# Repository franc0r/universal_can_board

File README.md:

# universal_can_board
Contains schematic, pcb layout and software of the francor's universal can board.

# Description
The universal board is used to control and monitor several components of a mobile robot like the motor controllers, co2 sensors, pan tilt unit, etc...

The board communicates via CAN interface. The used µC is a AVR from the Arduino Nano v2. Future more this board is based on an Arduino, so the Arduino IDE can be used to programm the board.

# Requirements
## Motor Controller
The BLD300B motor controller is used to drive the Robot Morty. This controller must be controlled and monitored by the board. For this following inputs and outputs are required.

* Input
  * An analog to measure current voltage of the motor controller.
  * An analog to measure current current of the motor controller.
  * Three digital to get the hall sensors of the hub motor wheels.
  * An digital to get the speed ticks from the motor controller.
* Output
  * An PWM to set the motor power.
  * An digital to set the rotation direction.
  * An digital to enable/disable the break.
  * An digital to enable/disable the motor controller.
  
## CO2 Sensor
The universal board should be able to measure the CO2 sensor and publish the values via CAN.

* Input
  * An analog to measure the current CO2 concentration.
  
* Output
  * An digital to indicate a high CO2 concentration. (drive a LED).

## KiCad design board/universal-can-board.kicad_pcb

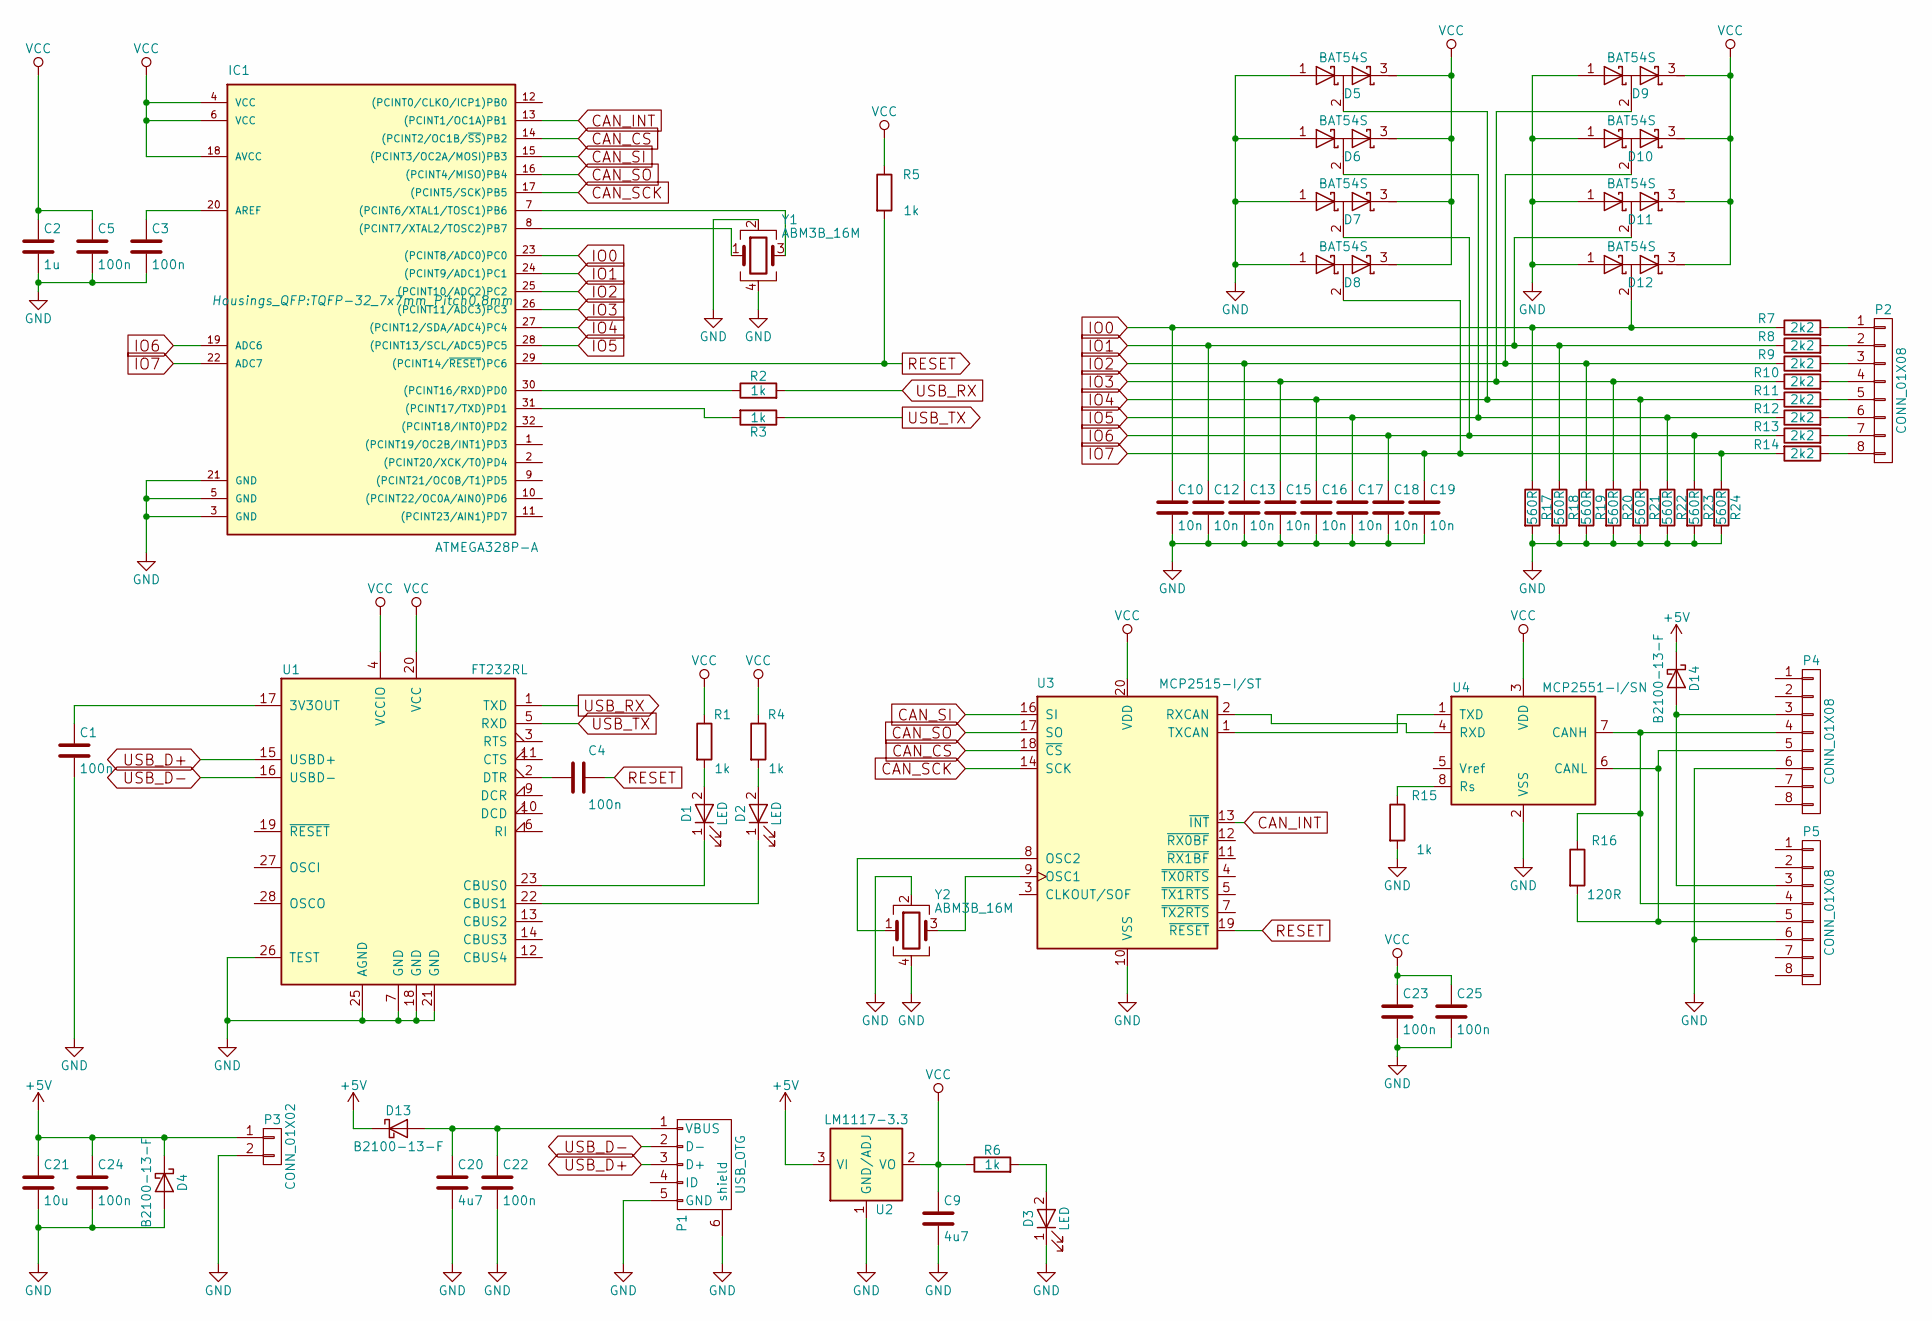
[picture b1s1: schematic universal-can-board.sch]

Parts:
C1, C3, C4, C5, C22, C23, C24, C25: 100n; C_0805
C2: 1u; C_0805
C9, C20: 4u7; C_1210
C10, C12, C13, C15, C16, C17, C18, C19: 10n; C_0805
C21: 10u; C_1210
D1, D2, D3: LED; LED_0805
D4, D13, D14: B2100-13-F; SMB_Standard
D5, D6, D7, D8, D9, D10, D11, D12: BAT54S; SOT-23
IC1: ATMEGA328P-A; TQFP-32_7x7mm_Pitch0.8mm
P1: USB_OTG; USB_Mini-B_Lumber_2486_Horizontal
P2: CONN_01X08; PhoenixContact_MSTBVA-G_08x5.08mm_Vertical
P3: CONN_01X02; PhoenixContact_MSTBVA-G_02x5.08mm_Vertical
P4, P5: CONN_01X08; RJ45_8
R1, R2, R3, R4, R5, R6, R15: 1k; R_0805
R7, R8, R9, R10, R11, R12, R13, R14: 2k2; R_0805
R16: 120R; R_0805
R17, R18, R19, R20, R21, R22, R23, R24: 560R; R_0805
U1: FT232RL; SSOP-28_5.3x10.2mm_Pitch0.65mm
U2: LM1117-3.3; SOT-223
U3: MCP2515-I/ST; TSSOP-20_4.4x6.5mm_Pitch0.65mm
U4: MCP2551-I/SN; SOIC-8_3.9x4.9mm_Pitch1.27mm
Y1, Y2: ABM3B_16M; Crystal_SMD_5032_4Pads

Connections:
+5V: C21.1, C24.1, D4.1 (K), D13.1 (K), D14.1 (K), P3.1, U2.3 (VI)
CAN_CS: IC1.14 ((PCINT2/OC1B/~SS~)PB2), U3.18 (~CS)
CAN_INT: IC1.13 ((PCINT1/OC1A)PB1), U3.13 (~INT)
CAN_SCK: IC1.17 ((PCINT5/SCK)PB5), U3.14 (SCK)
CAN_SI: IC1.15 ((PCINT3/OC2A/MOSI)PB3), U3.16 (SI)
CAN_SO: IC1.16 ((PCINT4/MISO)PB4), U3.17 (SO)
GND: C1.2, C2.2, C3.2, C5.2, C9.2, C10.2, C12.2, C13.2, C15.2, C16.2, C17.2, C18.2, C19.2, C20.2, C21.2, C22.2, C23.2, C24.2, C25.2, D3.1 (K), D4.2 (A), D5.1 (A), D6.1 (A), D7.1 (A), D8.1 (A), D9.1 (A), D10.1 (A), D11.1 (A), D12.1 (A), IC1.3 (GND), IC1.5 (GND), IC1.21 (GND), P1.5 (GND), P1.6 (shield), P3.2, P4.6, P5.6, R15.2, R17.2, R18.2, R19.2, R20.2, R21.2, R22.2, R23.2, R24.2, U1.7 (GND), U1.18 (GND), U1.21 (GND), U1.25 (AGND), U1.26 (TEST), U2.1 (GND/ADJ), U3.10 (VSS), U4.2 (VSS), Y1.2, Y1.4, Y2.2, Y2.4
IO0: C10.1, D12.2 (common), IC1.23 ((PCINT8/ADC0)PC0), R7.1, R17.1
IO1: C12.1, D11.2 (common), IC1.24 ((PCINT9/ADC1)PC1), R8.1, R18.1
IO2: C13.1, D10.2 (common), IC1.25 ((PCINT10/ADC2)PC2), R9.1, R19.1
IO3: C15.1, D9.2 (common), IC1.26 ((PCINT11/ADC3)PC3), R10.1, R20.1
IO4: C16.1, D5.2 (common), IC1.27 ((PCINT12/SDA/ADC4)PC4), R11.1, R21.1
IO5: C17.1, D6.2 (common), IC1.28 ((PCINT13/SCL/ADC5)PC5), R12.1, R22.1
IO6: C18.1, D7.2 (common), IC1.19 (ADC6), R13.1, R23.1
IO7: C19.1, D8.2 (common), IC1.22 (ADC7), R14.2, R24.1
unnamed: C1.1, U1.17 (3V3OUT)
unnamed: C3.1, IC1.20 (AREF)
unnamed: C4.2, U1.2 (DTR)
unnamed: C20.1, C22.1, D13.2 (A), P1.1 (VBUS)
unnamed: D1.1 (K), U1.23 (CBUS0)
unnamed: D1.2 (A), R1.2
unnamed: D2.1 (K), U1.22 (CBUS1)
unnamed: D2.2 (A), R4.2
unnamed: D3.2 (A), R6.2
unnamed: D14.2 (A), P4.3, P5.3
unnamed: IC1.7 ((PCINT6/XTAL1/TOSC1)PB6), Y1.3
unnamed: IC1.8 ((PCINT7/XTAL2/TOSC2)PB7), Y1.1
unnamed: IC1.30 ((PCINT16/RXD)PD0), R2.1
unnamed: IC1.31 ((PCINT17/TXD)PD1), R3.2
unnamed: P2.1, R7.2
unnamed: P2.2, R8.2
unnamed: P2.3, R9.2
unnamed: P2.4, R10.2
unnamed: P2.5, R11.2
unnamed: P2.6, R12.2
unnamed: P2.7, R13.2
unnamed: P2.8, R14.1
unnamed: P4.4, P5.4, R16.1, U4.7 (CANH)
unnamed: P4.5, P5.5, R16.2, U4.6 (CANL)
unnamed: R15.1, U4.8 (Rs)
unnamed: U3.1 (TXCAN), U4.1 (TXD)
unnamed: U3.2 (RXCAN), U4.4 (RXD)
unnamed: U3.8 (OSC2), Y2.1
unnamed: U3.9 (OSC1), Y2.3
RESET: C4.1, IC1.29 ((PCINT14/~RESET~)PC6), R5.2, U3.19 (~RESET)
USB_D+: P1.3 (D+), U1.15 (USBD+)
USB_D-: P1.2 (D-), U1.16 (USBD-)
USB_RX: R2.2, U1.1 (TXD)
USB_TX: R3.1, U1.5 (RXD)
VCC: C2.1, C5.1, C9.1, C23.1, C25.1, D5.3 (K), D6.3 (K), D7.3 (K), D8.3 (K), D9.3 (K), D10.3 (K), D11.3 (K), D12.3 (K), IC1.4 (VCC), IC1.6 (VCC), IC1.18 (AVCC), R1.1, R4.1, R5.1, R6.1, U1.4 (VCCIO), U1.20 (VCC), U2.2 (VO), U2.4 (VO), U3.20 (VDD), U4.3 (VDD)

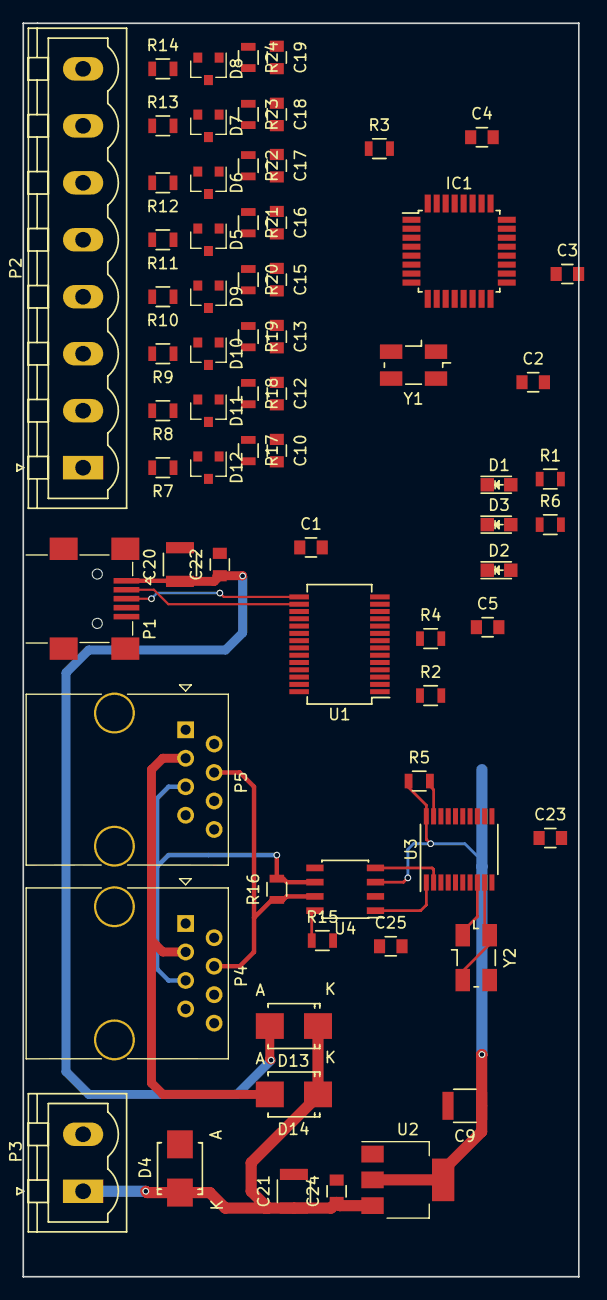
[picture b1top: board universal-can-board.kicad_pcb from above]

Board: 2 copper layers, 49.5 x 111.8 mm, 70 parts (0 on the bottom side), 50 nets.

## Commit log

2018-01-28 Created schematic of the board, including µC, USB FTDI and CAN controller + transreceiver. Review required.
2018-01-28 Added values to the board schematic.
2018-01-28 Removed conflicts in board schematic.
2018-01-29 Improved input circuit protection. Started with first version of the layout.
2018-02-07 Just saved new pcb layout try.
2018-02-08 Moved on with the layout.
2018-02-11 Routing of board v1.1
2018-02-11 Routing of PCB v1.1. All parts are placed now.
2018-02-15 Updated board layout.
2018-03-05 Added last missing parts and changed some routings.
2018-03-05 Added two mounting holes to the pcb.
2018-03-05 Flipped input filter C (CAN) from top to bottom.
2018-03-10 Added material bill for the motorcontroller controller.
2018-09-30 Moved standard board to atmega folder Create STM universal can board project
2018-10-04 Continued STM Board development
2018-10-06 Added comments and continued design (USB-UART converter)
